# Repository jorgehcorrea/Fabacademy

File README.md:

Welcome to your new Fab Academy site

This website is built automatically by gitlab every time you edit the files in the docs folder
It does so thanks to Mkdocs a static site generator written in Python
You must start customizing the file mkdocs.yml with your information
You can change the looks of your website using mkdocs themes, you can find in the mkdocs.yml the names of the available themes
If you want to start from scratch, you can delete everything in this repository and push any other static website

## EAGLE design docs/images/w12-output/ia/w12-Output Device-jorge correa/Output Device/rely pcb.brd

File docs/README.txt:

confirm

Editorial by HTML5 UP
html5up.net | @ajlkn
Free for personal and commercial use under the CCA 3.0 license (html5up.net/license)

Say hello to Editorial, a blog/magazine-ish template built around a toggleable "locking"
sidebar (scroll down to see what I mean) and an accordion-style menu. Not the usual landing
page/portfolio affair you'd expect to see at HTML5 UP, but I figured for my 41st (!!!)
template I'd change it up a little. Enjoy :)

Demo images* courtesy of Unsplash, a radtastic collection of CC0 (public domain) images
you can use for pretty much whatever.

(* = not included)

AJ
aj@lkn.io | @ajlkn

Credits:

	Demo Images:
		Unsplash (unsplash.com)

	Icons:
		Font Awesome (fontawesome.io)

	Other:
		jQuery (jquery.com)
		Responsive Tools (github.com/ajlkn/responsive-tools)

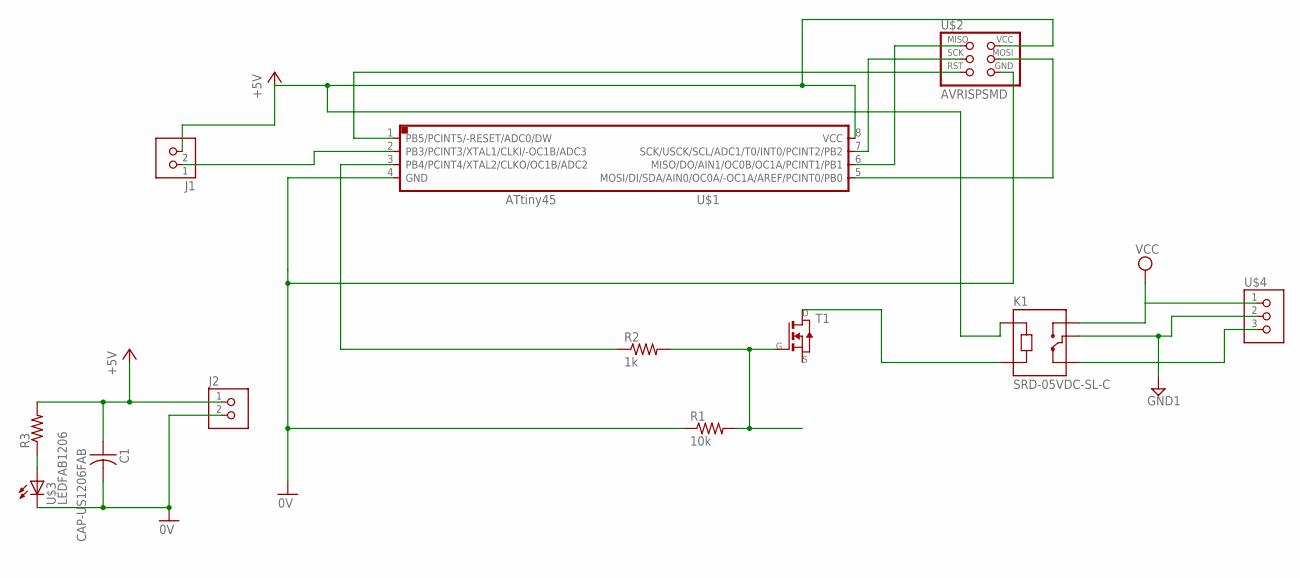
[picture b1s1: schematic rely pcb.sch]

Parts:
C1: CAP-US1206FAB; C1206FAB
J1, J2: TERM-1X02-ADAFRUIT; 3.5MMTERM
K1: SRD-05VDC-SL-C; RELAY_SRD-05VDC-SL-C
R1: 10k; R1206FAB
R2: 1k; R1206FAB
R3: RES-US1206FAB; R1206FAB
T1: NMOSFETTO252; TO252
U$1: ATTINY45SI; SOIC8
U$2: AVRISPSMD; 2X03SMD
U$3: LEDFAB1206; LED1206FAB
U$4: TERM-1X03'-FABLAB'; ED555DS-3DS

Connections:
0V: C1.2, J2.2, R1.1, U$1.4 (GND), U$2.6 (GND), U$3.2 (C)
+5V: C1.1, J1.2, J2.1, K1.A1, R3.2, U$1.8 (VCC), U$2.2 (VCC)
GND1: K1.COM, U$4.2
unnamed: U$1.6 (MISO/DO/AIN1/OC0B/OC1A/PCINT1/PB1), U$2.1 (MISO)
unnamed: U$1.5 (MOSI/DI/SDA/AIN0/OC0A/-OC1A/AREF/PCINT0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), U$2.4 (MOSI)
unnamed: R2.1, U$1.3 (PB4/PCINT4/XTAL2/CLKO/OC1B/ADC2)
unnamed: U$1.7 (SCK/USCK/SCL/ADC1/T0/INT0/PCINT2/PB2), U$2.3 (SCK)
unnamed: U$1.1 (PB5/PCINT5/-RESET/ADC0/DW), U$2.5 (RST)
unnamed: K1.A2, T1.3 (D)
unnamed: R1.2, R2.2, T1.1 (G)
unnamed: R3.1, U$3.1 (A)
unnamed: J1.1, U$1.2 (PB3/PCINT3/XTAL1/CLKI/-OC1B/ADC3)
unnamed: K1.NC, U$4.3
VCC: K1.NO, U$4.1

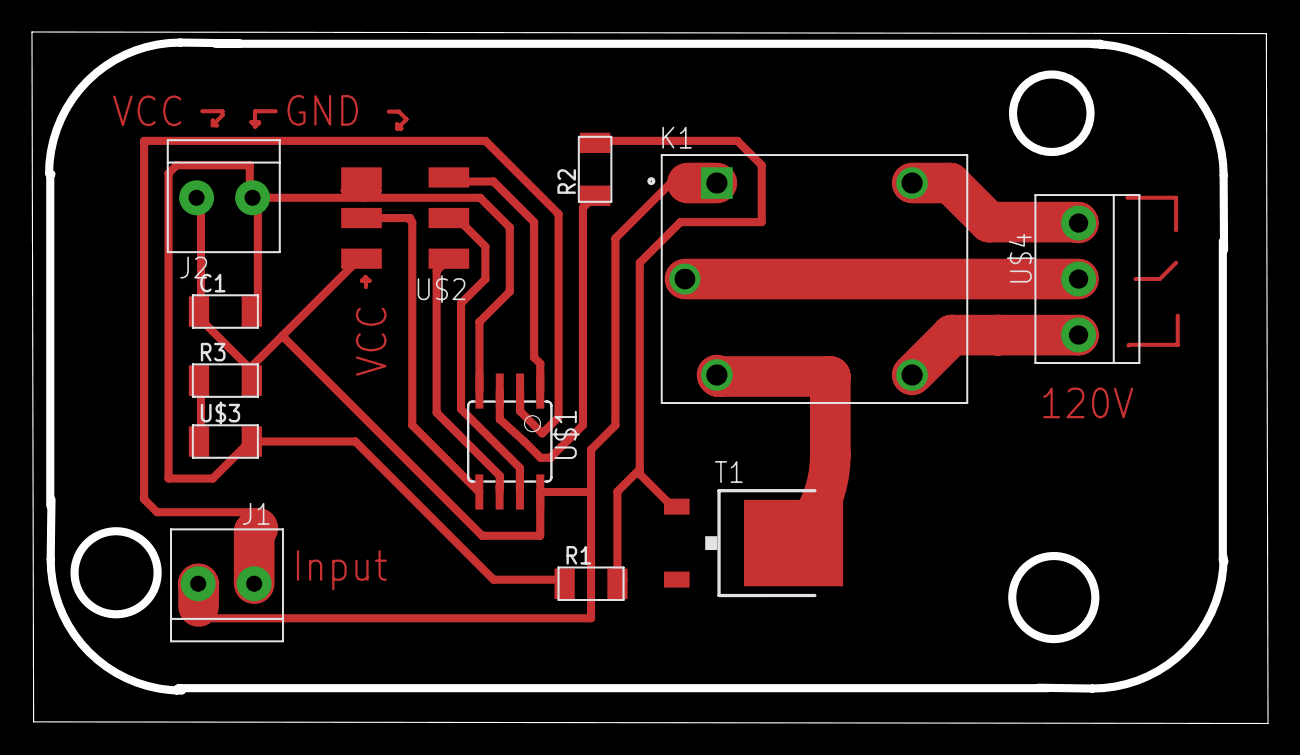
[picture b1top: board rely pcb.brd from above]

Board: 2 copper layers, 76.8 x 42.7 mm, 12 parts (0 on the bottom side), 14 nets.

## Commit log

2019-04-04 Add new file
2019-04-10 Readme - recovering
2019-04-10 .gitignore - recovering
2019-04-10 requirements - recovering
2019-04-10 .gitlab-ci.yml - recovering
2019-04-10 mkdocs.yml - recovering
2019-04-13 Added a new docs folder
2019-04-13 added new index
2019-04-13 index.html test
2019-04-13 w12 update
2019-04-13 index update
2019-04-15 w-13 update
2019-04-21 week 4 update
2019-04-21 size update
2019-04-22 w10 update
2019-04-22 w10 video update
2019-05-03 w-12 update
2019-05-05 w 13 update
2019-05-08 w 15 update
2019-05-08 w15 update 2
2019-05-08 w-15 update
2019-05-08 w-15 update2
2019-05-08 w-15 update3
2019-05-13 w2 update
2019-05-13 w2-update
2019-05-13 project update
2019-05-13 w2 & w8 update
2019-05-14 w8 video update
2019-05-14 w8 update2gif
2019-05-15 w16 create and update
2019-05-15 w-16 links update
2019-05-17 w3 update
2019-05-19 w13 images
2019-05-25 w13 update + w2 update
2019-05-26 w5&w6 update
2019-05-26 w6 update
2019-05-26 w-4 update
2019-05-26 w-6 update
2019-05-26 w-update
2019-06-08 presentation slide + w17
2019-06-09 up slide
2019-06-09 video presentation
2019-06-09 video swap, 1080p to 720
2019-06-09 welcome video update
2019-06-10 index update loop
2019-06-11 final project per week update
2019-06-12 sound update, on video and images proejct
2019-06-12 update videos and stuff
2019-06-12 w-21 update
2019-06-12 minor change update
2019-06-12 links updates
2019-06-14 w update
2019-06-15 fp update
2019-06-15 link updates
2019-06-15 final project development
2019-06-15 w19 update
2019-06-16 w fp update, bom
2019-06-16 W 19 update
2019-06-16 w fp update
2019-06-16 w-18 update
2019-06-17 w 17 update
2019-06-17 w 17 update 2
2019-06-17 update w18/19
2019-06-17 w19 udpate
2019-06-17 license update
2019-06-17 w19 updates
2019-06-17 w16 update add the process app
2019-06-17 w-16 update
2019-06-17 w16 update
2019-06-17 w17 update
2019-06-17 tag stuff
2019-06-17 w19 update links
2019-06-17 update links
2019-06-17 update unlinked images to root folder
2019-06-17 links
2019-06-17 update w19
2019-06-19 w14 update
2019-06-19 some other weeks update
2019-06-20 w11 update
2019-06-21 w4 update
2019-06-21 w 5 update
2019-06-21 w5 little coma update
2019-06-22 Update assignment-15.html - Added stl
2019-06-22 Upload v5-stl .zip files
2019-06-22 Update assignment-15.html ?
2019-06-22 Update assignment-15.html #2 Link update
2019-06-22 Update assignment-15.html link update 2
2019-06-23 casted positive img upload
2019-06-23 Upload New File
2019-06-26 Upload New File - Scan of myself
2019-06-30 Add new directory
